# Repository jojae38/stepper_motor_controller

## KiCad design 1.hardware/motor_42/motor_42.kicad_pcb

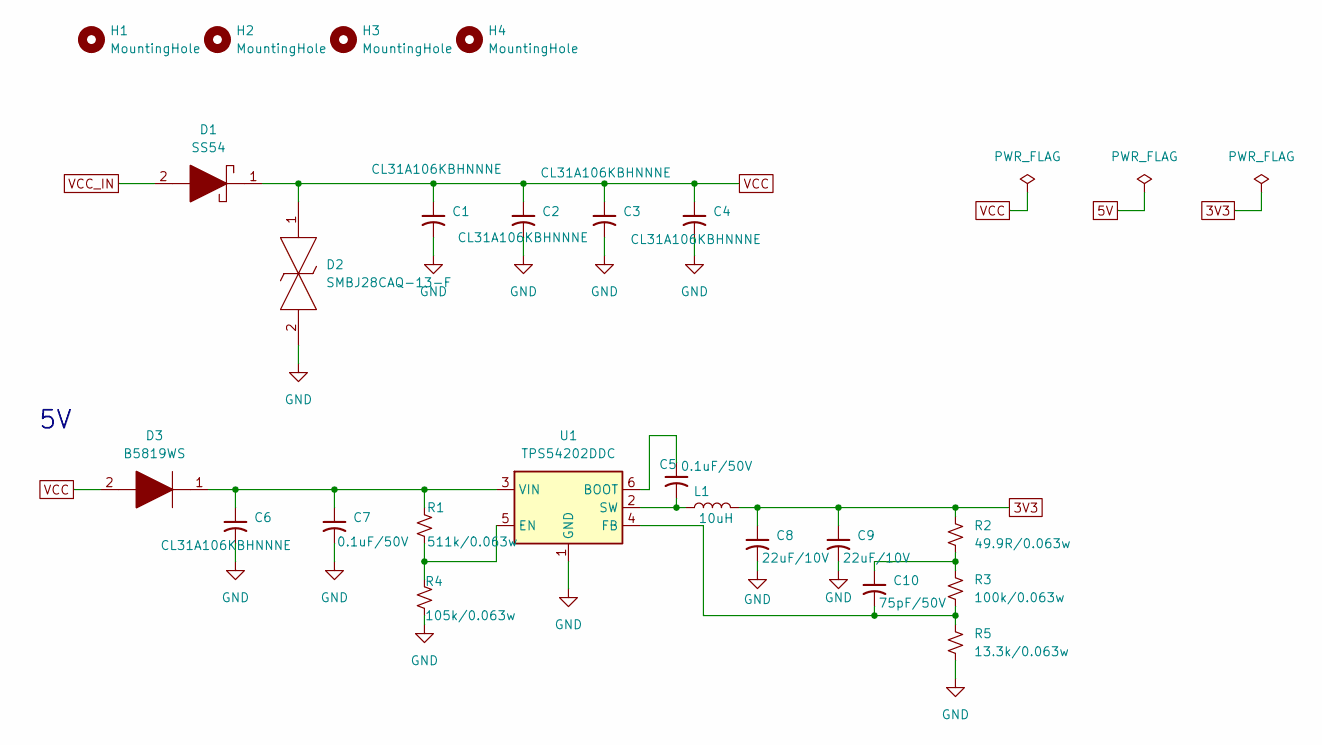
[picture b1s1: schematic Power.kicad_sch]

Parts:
C1, C2, C3, C4, C6: CL31A106KBHNNNE; C_1206_3216Metric
C5, C7: 0.1uF/50V; C_0402_1005Metric
C8, C9: 22uF/10V; C_1206_3216Metric
C10: 75pF/50V; C_0402_1005Metric
D1: SS54; DIOM5126X245N; Manufacturer_Part_Number SS54
D2: SMBJ28CAQ-13-F; DIONM5336X250N; Manufacturer_Part_Number SMBJ28CAQ-13-F; Mouser Part Number 621-SMBJ28CAQ-13-F
D3: B5819WS; D_SOD-323; Manufacturer_Part_Number B5819WS
H1, H2, H3, H4: MountingHole; MountingHole_3.2mm_M3
L1: 10uH; L_Sunlord_SWPA4020S
R1: 511k/0.063w; R_0402_1005Metric
R2: 49.9R/0.063w; R_0402_1005Metric
R3: 100k/0.063w; R_0402_1005Metric
R4: 105k/0.063w; R_0402_1005Metric
R5: 13.3k/0.063w; R_0402_1005Metric
U1: TPS54202DDC; SOT-23-6

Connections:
3V3: C8.1, C9.1, L1.2, R2.1; also elsewhere on the board
GND: C1.2, C2.2, C3.2, C4.2, C6.2, C7.2, C8.2, C9.2, D2.2, R4.2, R5.2, U1.1 (GND); also elsewhere on the board
unnamed: C10.1, R2.2, R3.1
unnamed: C5.1, U1.6 (BOOT)
unnamed: R1.2, R4.1, U1.5 (EN)
unnamed: C10.2, R3.2, R5.1, U1.4 (FB)
unnamed: C5.2, L1.1, U1.2 (SW)
unnamed: C6.1, C7.1, D3.1, R1.1, U1.3 (VIN)
VCC: C1.1, C2.1, C3.1, C4.1, D1.1, D2.1, D3.2; also elsewhere on the board
VCC_IN: D1.2; also elsewhere on the board

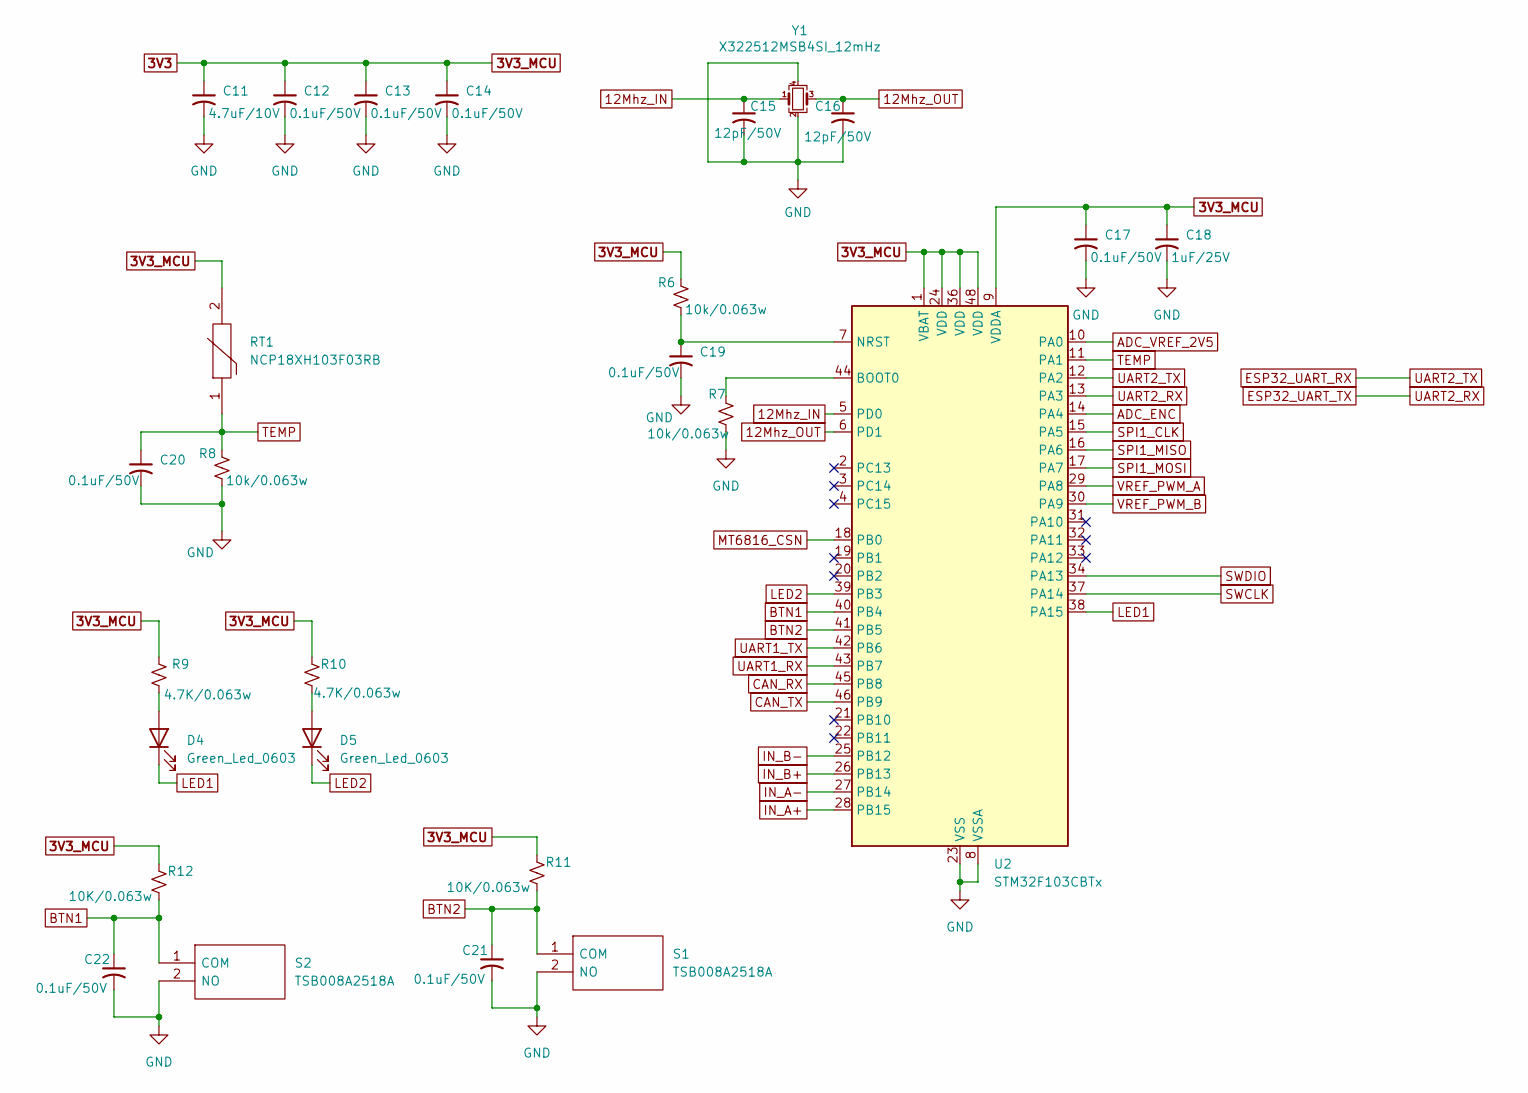
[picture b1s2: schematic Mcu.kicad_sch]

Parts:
C11: 4.7uF/10V; C_0603_1608Metric
C12, C13, C14, C17, C19, C20, C21, C22: 0.1uF/50V; C_0402_1005Metric
C15, C16: 12pF/50V; C_0402_1005Metric
C18: 1uF/25V; C_0402_1005Metric
D4, D5: Green_Led_0603; LED_0603_1608Metric
R6, R7, R8: 10k/0.063w; R_0402_1005Metric
R9, R10: 4.7K/0.063w; R_0402_1005Metric
R11, R12: 10K/0.063w; R_0402_1005Metric
RT1: NCP18XH103F03RB; THRMC1608X95N; Manufacturer_Part_Number NCP18XH103F03RB; Mouser Part Number 81-NCP18XH103F03RB
S1, S2: TSB008A2518A; Manufacturer_Part_Number TSB008A2518A
U2: STM32F103CBTx; LQFP-48_7x7mm_P0.5mm
Y1: X322512MSB4SI_12mHz; Crystal_SMD_3225-4Pin_3.2x2.5mm

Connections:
3V3: C11.1, C12.1, C13.1, C14.1, C17.1, C18.1, R6.2, R9.1, R10.1, R11.1, R12.1, RT1.2, U2.1 (VBAT), U2.9 (VDDA), U2.24 (VDD), U2.36 (VDD), U2.48 (VDD); also elsewhere on the board
12Mhz_IN: C15.1, U2.5 (PD0), Y1.1
12Mhz_OUT: C16.1, U2.6 (PD1), Y1.3
ADC_ENC: U2.14 (PA4); also elsewhere on the board
ADC_VREF_2V5: U2.10 (PA0); also elsewhere on the board
BTN1: C22.1, R12.2, S2.1 (COM), U2.40 (PB4)
BTN2: C21.1, R11.2, S1.1 (COM), U2.41 (PB5)
CAN_RX: U2.45 (PB8); also elsewhere on the board
CAN_TX: U2.46 (PB9); also elsewhere on the board
ESP32_UART_RX: U2.12 (PA2); also elsewhere on the board
ESP32_UART_TX: U2.13 (PA3); also elsewhere on the board
GND: C11.2, C12.2, C13.2, C14.2, C15.2, C16.2, C17.2, C18.2, C19.2, C20.2, C21.2, C22.2, R7.2, R8.1, S1.2 (NO), S2.2 (NO), U2.8 (VSSA), U2.23 (VSS), U2.35 (VSS), U2.47 (VSS), Y1.2, Y1.4; also elsewhere on the board
IN_A+: U2.28 (PB15); also elsewhere on the board
IN_A-: U2.27 (PB14); also elsewhere on the board
IN_B+: U2.26 (PB13); also elsewhere on the board
IN_B-: U2.25 (PB12); also elsewhere on the board
LED1: D4.1 (K), U2.38 (PA15)
LED2: D5.1 (K), U2.39 (PB3)
MT6816_CSN: U2.18 (PB0); also elsewhere on the board
unnamed: D4.2 (A), R9.2
unnamed: D5.2 (A), R10.2
unnamed: R7.1, U2.44 (BOOT0)
unnamed: C19.1, R6.1, U2.7 (NRST)
SPI1_CLK: U2.15 (PA5); also elsewhere on the board
SPI1_MISO: U2.16 (PA6); also elsewhere on the board
SPI1_MOSI: U2.17 (PA7); also elsewhere on the board
SWCLK: U2.37 (PA14); also elsewhere on the board
SWDIO: U2.34 (PA13); also elsewhere on the board
TEMP: C20.1, R8.2, RT1.1, U2.11 (PA1)
UART1_RX: U2.43 (PB7); also elsewhere on the board
UART1_TX: U2.42 (PB6); also elsewhere on the board
VREF_PWM_A: U2.29 (PA8); also elsewhere on the board
VREF_PWM_B: U2.30 (PA9); also elsewhere on the board

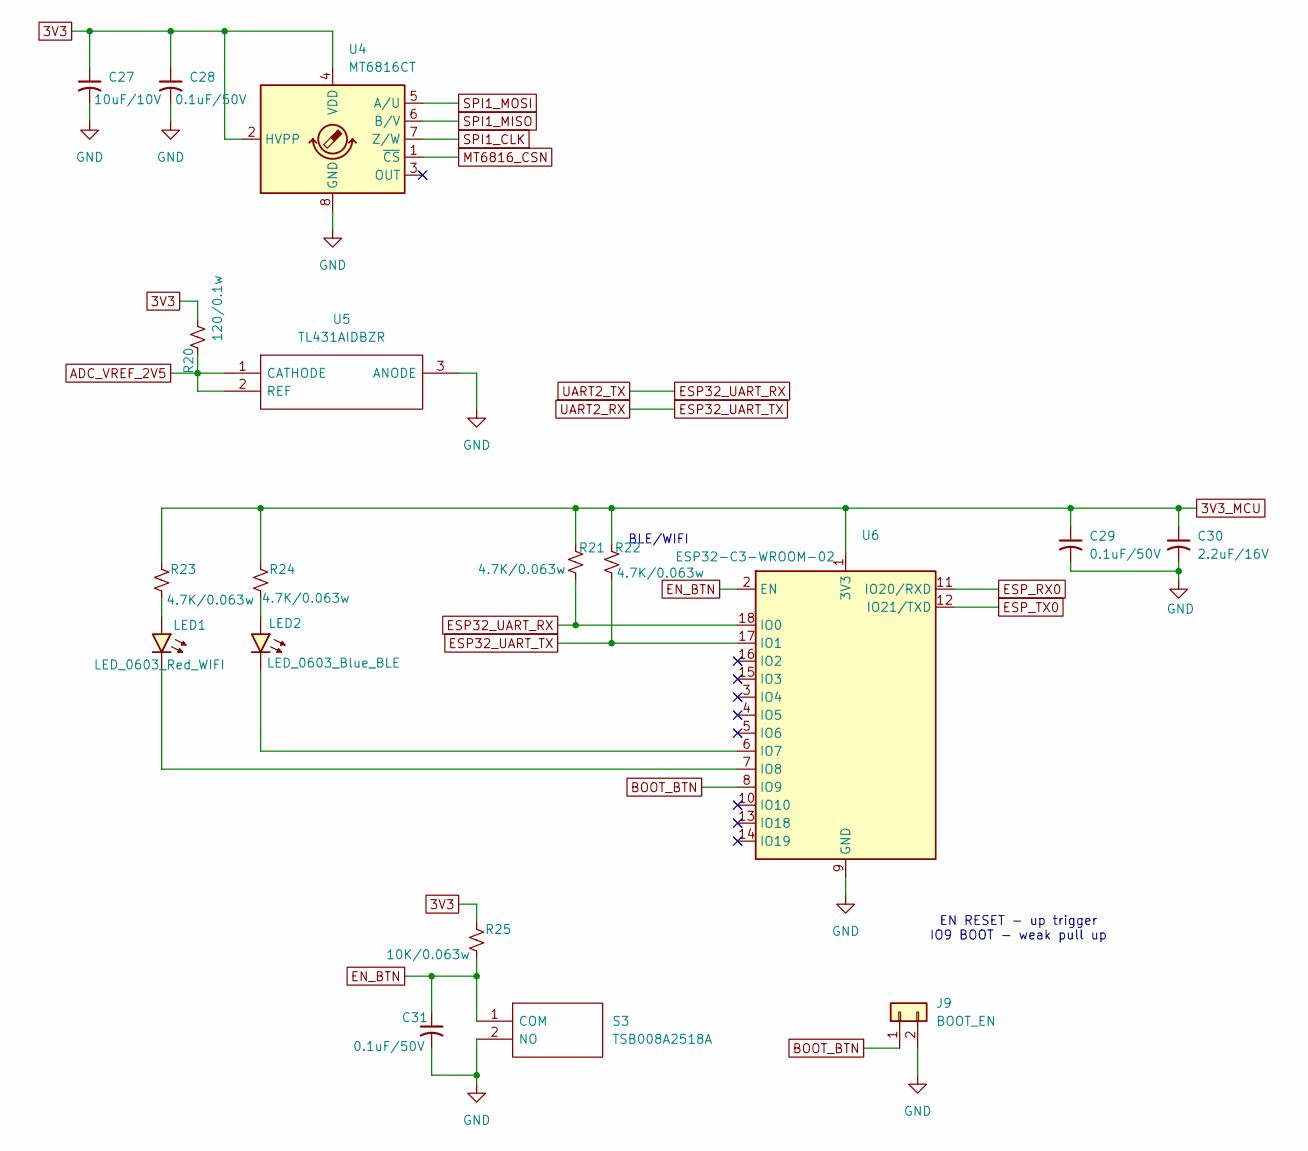
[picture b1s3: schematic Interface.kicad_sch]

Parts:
C27: 10uF/10V; C_0603_1608Metric
C28, C29, C31: 0.1uF/50V; C_0402_1005Metric
C30: 2.2uF/16V; C_0603_1608Metric
J9: BOOT_EN; PinHeader_1x02_P2.54mm_Vertical
LED1: LED_0603_Red_WIFI; LED_0603_1608Metric
LED2: LED_0603_Blue_BLE; LED_0603_1608Metric
R20: 120/0.1w; R_0603_1608Metric
R21, R22, R23, R24: 4.7K/0.063w; R_0402_1005Metric
R25: 10K/0.063w; R_0402_1005Metric
S3: TSB008A2518A; Manufacturer_Part_Number TSB008A2518A
U4: MT6816CT; SO-8_3.9x4.9mm_P1.27mm
U5: TL431AIDBZR; SOT95P237X112-3N; Manufacturer_Part_Number TL431AIDBZR; Mouser Part Number 595-TL431AIDBZR
U6: ESP32-C3-WROOM-02

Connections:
3V3: C27.1, C28.1, C29.1, C30.1, R20.1, R21.1, R22.1, R23.1, R24.1, R25.1, U4.2 (HVPP), U4.4 (VDD), U6.1 (3V3); also elsewhere on the board
ADC_VREF_2V5: R20.2, U5.1 (CATHODE), U5.2 (REF); also elsewhere on the board
BOOT_BTN: J9.1, U6.8 (IO9)
EN_BTN: C31.1, R25.2, S3.1 (COM), U6.2 (EN)
ESP32_UART_RX: R21.2, U6.18 (IO0); also elsewhere on the board
ESP32_UART_TX: R22.2, U6.17 (IO1); also elsewhere on the board
ESP_RX0: U6.11 (IO20/RXD); also elsewhere on the board
ESP_TX0: U6.12 (IO21/TXD); also elsewhere on the board
GND: C27.2, C28.2, C29.2, C30.2, C31.2, J9.2, S3.2 (NO), U4.8 (GND), U5.3 (ANODE), U6.9 (GND), U6.19 (GND); also elsewhere on the board
MT6816_CSN: U4.1 (~CS); also elsewhere on the board
unnamed: LED1.2 (A), R23.2
unnamed: LED1.1 (K), U6.7 (IO8)
unnamed: LED2.2 (A), R24.2
unnamed: LED2.1 (K), U6.6 (IO7)
SPI1_CLK: U4.7 (Z/W); also elsewhere on the board
SPI1_MISO: U4.6 (B/V); also elsewhere on the board
SPI1_MOSI: U4.5 (A/U); also elsewhere on the board

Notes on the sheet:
BLE/WIFI
EN RESET - up trigger IO9 BOOT - weak pull up

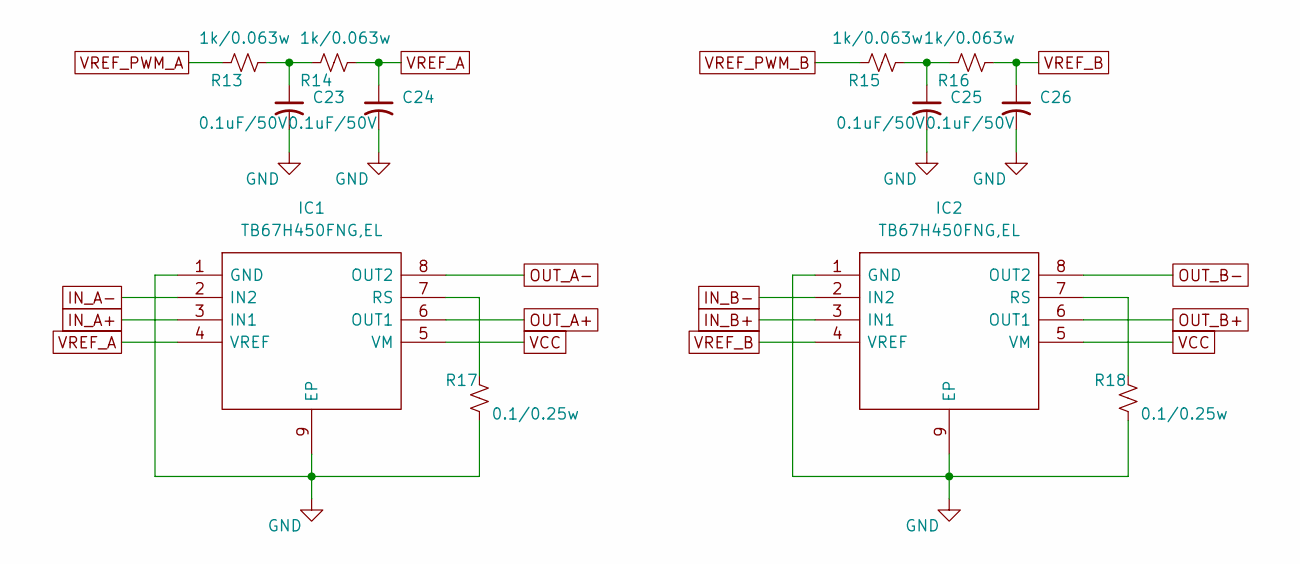
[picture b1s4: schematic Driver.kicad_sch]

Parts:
C23, C24, C25, C26: 0.1uF/50V; C_0402_1005Metric
IC1, IC2: TB67H450FNG,EL; SOIC127P600X175-9N; Manufacturer_Part_Number TB67H450FNG,EL; Mouser Part Number 757-TB67H450FNGEL
R13, R14, R15, R16: 1k/0.063w; R_0402_1005Metric
R17, R18: 0.1/0.25w; R_1206_3216Metric

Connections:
GND: C23.2, C24.2, C25.2, C26.2, IC1.1 (GND), IC1.9 (EP), IC2.1 (GND), IC2.9 (EP), R17.1, R18.1; also elsewhere on the board
IN_A+: IC1.3 (IN1); also elsewhere on the board
IN_A-: IC1.2 (IN2); also elsewhere on the board
IN_B+: IC2.3 (IN1); also elsewhere on the board
IN_B-: IC2.2 (IN2); also elsewhere on the board
unnamed: C23.1, R13.1, R14.2
unnamed: C25.1, R15.1, R16.2
unnamed: IC1.7 (RS), R17.2
unnamed: IC2.7 (RS), R18.2
OUT_A+: IC1.6 (OUT1); also elsewhere on the board
OUT_A-: IC1.8 (OUT2); also elsewhere on the board
OUT_B+: IC2.6 (OUT1); also elsewhere on the board
OUT_B-: IC2.8 (OUT2); also elsewhere on the board
VCC: IC1.5 (VM), IC2.5 (VM); also elsewhere on the board
VREF_A: C24.1, IC1.4 (VREF), R14.1
VREF_B: C26.1, IC2.4 (VREF), R16.1
VREF_PWM_A: R13.2; also elsewhere on the board
VREF_PWM_B: R15.2; also elsewhere on the board

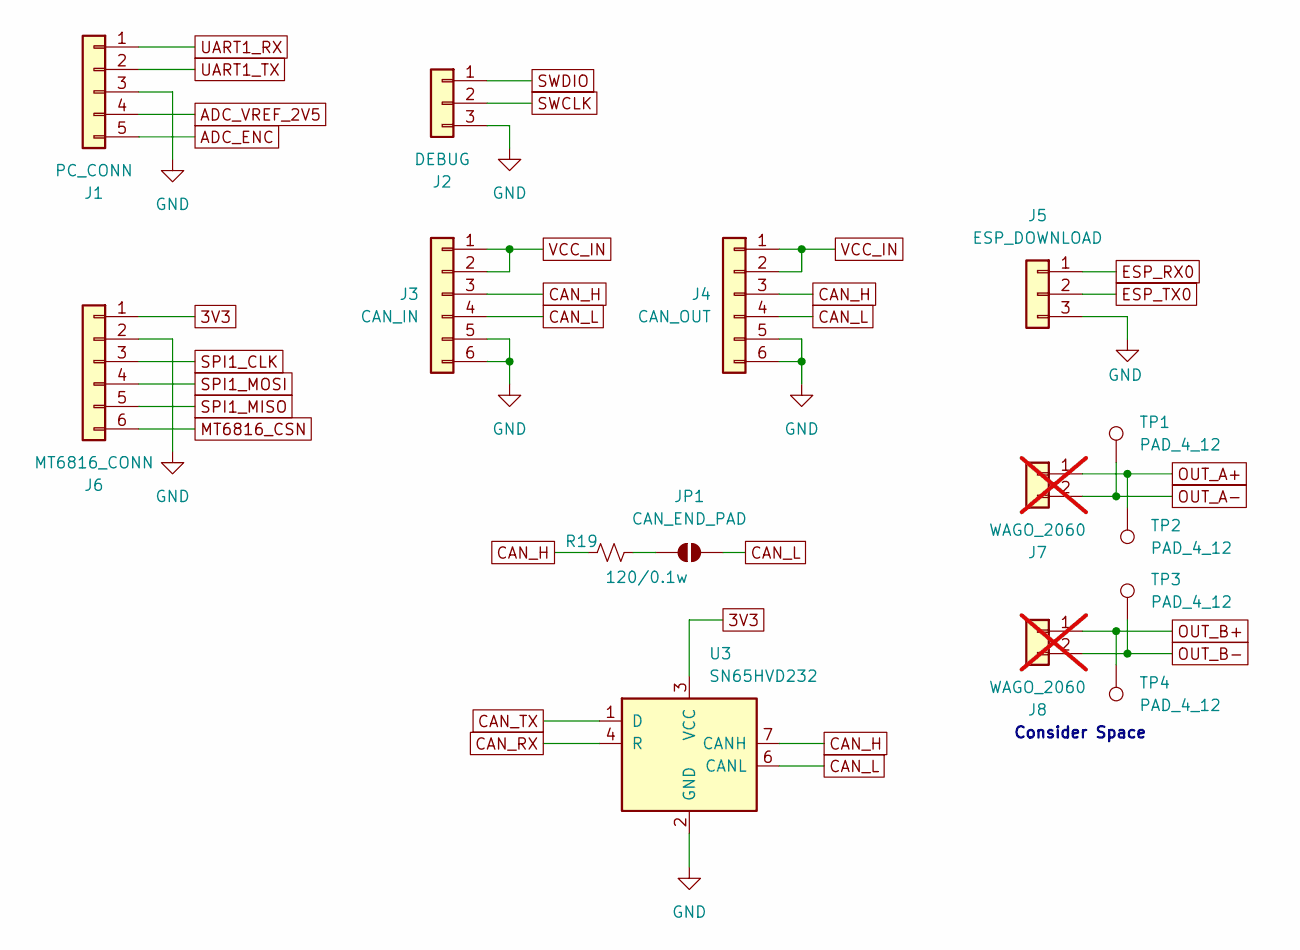
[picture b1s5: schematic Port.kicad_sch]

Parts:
J1: PC_CONN; JST_SH_SM05B-SRSS-TB_1x05-1MP_P1.00mm_Horizontal
J2: DEBUG; JST_SH_SM03B-SRSS-TB_1x03-1MP_P1.00mm_Horizontal
J3: CAN_IN; JST_SH_SM06B-SRSS-TB_1x06-1MP_P1.00mm_Horizontal
J4: CAN_OUT; JST_SH_SM06B-SRSS-TB_1x06-1MP_P1.00mm_Horizontal
J5: ESP_DOWNLOAD; JST_SH_SM03B-SRSS-TB_1x03-1MP_P1.00mm_Horizontal
J6: MT6816_CONN; JST_SH_SM05B-SRSS-TB_1x05-1MP_P1.00mm_Horizontal
J7, J8: WAGO_2060; not fitted
JP1: CAN_END_PAD; SolderJumper-2_P1.3mm_Open_RoundedPad1.0x1.5mm
R19: 120/0.1w; R_0603_1608Metric
TP1, TP2, TP3, TP4: PAD_4_12; custom_pad_2_5
U3: SN65HVD232; SOIC-8_3.9x4.9mm_P1.27mm

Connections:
3V3: J6.1, U3.3 (VCC); also elsewhere on the board
ADC_ENC: J1.5; also elsewhere on the board
ADC_VREF_2V5: J1.4; also elsewhere on the board
CAN_H: J3.3, J4.3, R19.2, U3.7 (CANH)
CAN_L: J3.4, J4.4, JP1.2 (B), U3.6 (CANL)
CAN_RX: U3.4 (R); also elsewhere on the board
CAN_TX: U3.1 (D); also elsewhere on the board
ESP_RX0: J5.1; also elsewhere on the board
ESP_TX0: J5.2; also elsewhere on the board
GND: J1.3, J2.3, J3.5, J3.6, J4.5, J4.6, J5.3, J6.2, U3.2 (GND); also elsewhere on the board
unnamed: JP1.1 (A), R19.1
OUT_A+: J7.1, TP2.1; also elsewhere on the board
OUT_A-: J7.2, TP1.1; also elsewhere on the board
OUT_B+: J8.1, TP4.1; also elsewhere on the board
OUT_B-: J8.2, TP3.1; also elsewhere on the board
SPI1_CLK: J6.3; also elsewhere on the board
SPI1_MISO: J6.5; also elsewhere on the board
SPI1_MOSI: J6.4; also elsewhere on the board
SWCLK: J2.2; also elsewhere on the board
SWDIO: J2.1; also elsewhere on the board
UART1_RX: J1.1; also elsewhere on the board
UART1_TX: J1.2; also elsewhere on the board
VCC_IN: J3.1, J3.2, J4.1, J4.2; also elsewhere on the board

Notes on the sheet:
Consider Space

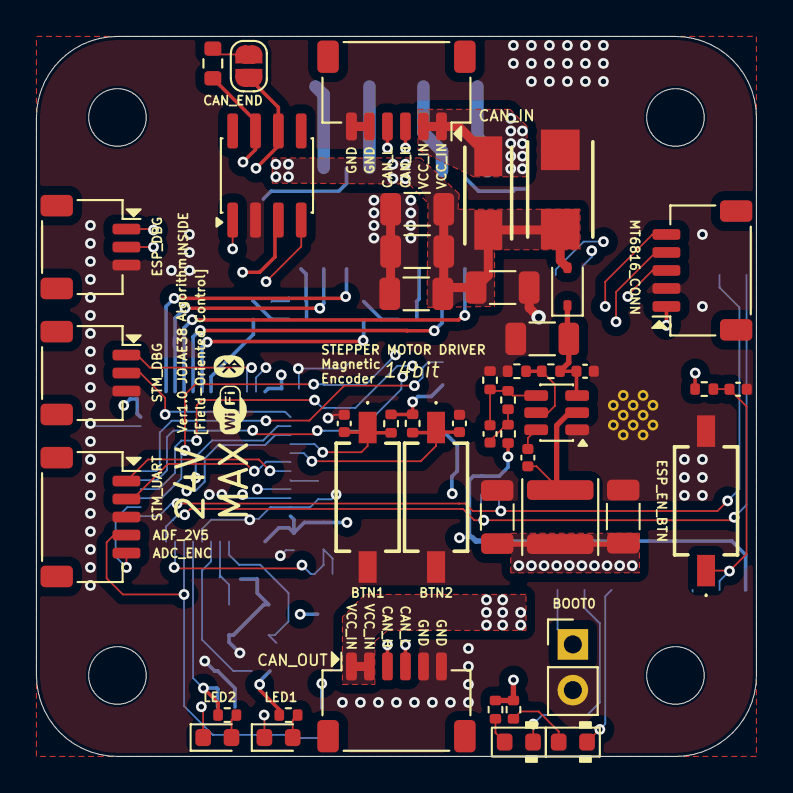
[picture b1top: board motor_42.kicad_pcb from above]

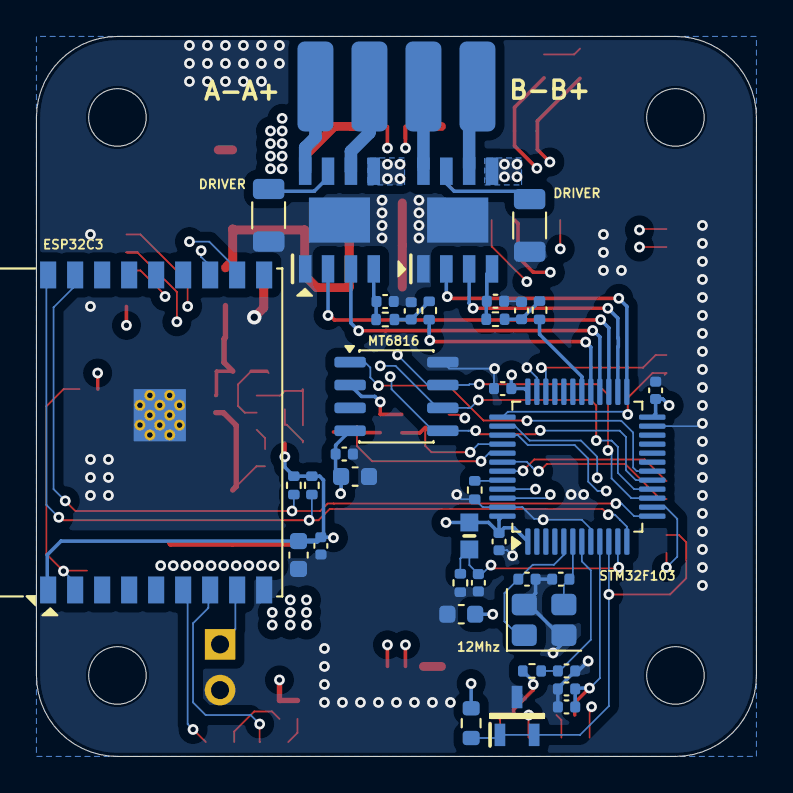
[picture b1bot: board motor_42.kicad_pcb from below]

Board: 4 copper layers, 40.0 x 40.0 mm, 93 parts (42 on the bottom side), 62 nets.

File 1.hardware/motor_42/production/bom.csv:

Designator,Footprint,Quantity,Value,LCSC Part #
"C10, C2, C6, C7, C8",1206,5,CL31A106KBHNNNE,
"C11, C12",1206,2,22uF/10V,
C13,0402,1,75pF/50V,
"C14, C15, C17, C18, C19, C20, C21, C24, C25, C26, C27, C30, C31, C32, C35, C4, C9",0402,17,0.1uF/50V,
C16,0603,1,4.7uF/10V,
"C22, C23",0402,2,12pF/50V,
C28,0603,1,10uF/6.3V,
C33,0603,1,2.2uF/6.3V,
C36,0402,1,1uF/10V,
D2,DIONM5336X250N,1,SMBJ28CAQ-13-F,
D3,D_SOD-323,1,B5819WS,
D4,DIOM5126X245N,1,SS54,
"IC1, IC2",SOIC127P600X175-9N,2,"TB67H450FNG,EL",
J1,JST_SH_SM05B-SRSS-TB_1x05-1MP_P1.00mm_Horizontal,1,PC_CONN,
J2,JST_SH_SM05B-SRSS-TB_1x05-1MP_P1.00mm_Horizontal,1,MT6816_CONN,
J4,JST_SH_SM03B-SRSS-TB_1x03-1MP_P1.00mm_Horizontal,1,DEBUG,
J5,JST_SH_SM06B-SRSS-TB_1x06-1MP_P1.00mm_Horizontal,1,CAN_IN,
J6,JST_SH_SM06B-SRSS-TB_1x06-1MP_P1.00mm_Horizontal,1,CAN_OUT,
J7,JST_SH_SM03B-SRSS-TB_1x03-1MP_P1.00mm_Horizontal,1,ESP_DOWNLOAD,
J8,PinHeader_1x02_P2.54mm_Vertical,1,BOOT_EN,
L2,L_Sunlord_SWPA4020S,1,10uH,
"LED1, LED4",0603,2,LED_0603_Red_WIFI,
"LED2, LED5",0603,2,LED_0603_Blue_BLE,
R1,0402,1,511k/0.063w,
"R10, R11, R13, R14, R15, R32",0402,6,10k/0.063w,
"R12, R28, R31, R33, R34, R9",0402,6,4.7K/0.063w,
"R18, R19, R21, R22",0402,4,1k/0.063w,
R2,0402,1,105k/0.063w,
"R20, R23",1206,2,0.1/0.25w,
"R26, R29",0603,2,120/0.1w,
R6,0402,1,49.9R/0.063w,
R7,0402,1,100k/0.063w,
R8,0402,1,13.3k/0.063w,
RT1,THRMC1608X95N,1,NCP18XH103F03RB,
"S1, S2, S3",TSB008A2518A,3,TSB008A2518A,
"TP1, TP2, TP3, TP4",custom_pad_2_5,4,PAD_4_12,
U1,SOT-23-6,1,TPS54202DDC,
U2,LQFP-48_7x7mm_P0.5mm,1,STM32F103CBTx,
U3,SOIC-8_3.9x4.9mm_P1.27mm,1,SN65HVD232,
U4,SOT95P237X112-3N,1,TL431AIDBZR,
U5,SO-8_3.9x4.9mm_P1.27mm,1,MT6816CT,
U6,ESP32-C3-WROOM-02,1,ESP32-C3-WROOM-02,
Y1,Crystal_SMD_3225-4Pin_3.2x2.5mm,1,YSX321SL_12Mhz,

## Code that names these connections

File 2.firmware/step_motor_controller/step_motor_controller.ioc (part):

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Mcu.Name=STM32F103C(8-B)Tx
Mcu.Package=LQFP48
Mcu.UserName=STM32F103CBTx
PA0-WKUP.GPIOParameters=GPIO_Label
PA0-WKUP.GPIO_Label=ADC1_0_VREF_2V5
PA0-WKUP.Signal=ADCx_IN0
PA1.GPIOParameters=GPIO_Label
PA1.GPIO_Label=ADC1_1_TEMP
PA1.Signal=ADCx_IN1
PA11.GPIOParameters=GPIO_Label
PA11.GPIO_Label=NC_USB_DM
PA11.Mode=Device
PA11.Signal=USB_DM
PA12.GPIOParameters=GPIO_Label
PA12.GPIO_Label=NC_USB_DP
PA12.Mode=Device
PA12.Signal=USB_DP
PA13.Mode=Serial_Wire
PA13.Signal=SYS_JTMS-SWDIO
PA14.Mode=Serial_Wire
PA14.Signal=SYS_JTCK-SWCLK
PA15.GPIOParameters=PinState,GPIO_Label
PA15.GPIO_Label=LED1
PA15.PinState=GPIO_PIN_SET
PA15.Signal=GPIO_Output
PA2.GPIOParameters=GPIO_Label
PA2.GPIO_Label=UART2_TX_ESP32
PA2.Mode=Asynchronous
PA2.Signal=USART2_TX
PA3.GPIOParameters=GPIO_Label
PA3.GPIO_Label=UART2_RX_ESP32
PA3.Mode=Asynchronous
PA3.Signal=USART2_RX
PA4.GPIOParameters=GPIO_Label
PA4.GPIO_Label=ADC_ENC
PA4.Signal=GPIO_Output
PA5.Mode=Full_Duplex_Slave
PA5.Signal=SPI1_SCK
PA6.Mode=Full_Duplex_Slave
PA6.Signal=SPI1_MISO
PA7.Mode=Full_Duplex_Slave
PA7.Signal=SPI1_MOSI
PA8.GPIOParameters=GPIO_Label
PA8.GPIO_Label=VREF_PWM_A
PA8.Signal=S_TIM1_CH1
PA9.GPIOParameters=GPIO_Label
PA9.GPIO_Label=VREF_PWM_B
PA9.Signal=S_TIM1_CH2
PB0.GPIOParameters=GPIO_Label
PB0.GPIO_Label=MT6816_CSN
PB0.Signal=GPIO_Output
PB12.GPIOParameters=GPIO_Label
PB12.GPIO_Label=IN_B_M
PB12.Signal=GPIO_Output
PB13.GPIOParameters=GPIO_Label
PB13.GPIO_Label=IN_B_P
PB13.Signal=GPIO_Output
PB14.GPIOParameters=GPIO_Label
PB14.GPIO_Label=IN_A_M
PB14.Signal=GPIO_Output
PB15.GPIOParameters=GPIO_Label
PB15.GPIO_Label=IN_A_P
PB15.Signal=GPIO_Output
PB3.GPIOParameters=PinState,GPIO_Label
PB3.GPIO_Label=LED2
PB3.PinState=GPIO_PIN_SET
PB3.Signal=GPIO_Output
PB4.GPIOParameters=GPIO_Label
PB4.GPIO_Label=BTN1
PB4.Signal=GPIO_Input
PB5.GPIOParameters=GPIO_Label
PB5.GPIO_Label=BTN2
PB5.Signal=GPIO_Input
PB6.Mode=Asynchronous
PB6.Signal=USART1_TX
PB7.Mode=Asynchronous
PB7.Signal=USART1_RX
PB8.Mode=CAN_Activate
PB8.Signal=CAN_RX
PB9.Mode=CAN_Activate
PB9.Signal=CAN_TX
PD0-OSC_IN.Mode=HSE-External-Oscillator
PD0-OSC_IN.Signal=RCC_OSC_IN
PD1-OSC_OUT.Mode=HSE-External-Oscillator
PD1-OSC_OUT.Signal=RCC_OSC_OUT
RCC.HSE_VALUE=12000000
RCC.SYSCLKFreq_VALUE=72000000
RCC.SYSCLKSource=RCC_SYSCLKSOURCE_PLLCLK
board=custom

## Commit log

2025-11-09 first_commit
2025-11-18 중간 저장
2025-11-26 살짝 변경
2025-11-27 작은 변경
2025-11-29 회로도 대충 완성
2025-11-30 3V3 LDO변경 및 대략적 위치 세팅
2025-12-01 얼추 다 그림
2025-12-01 실크 업데이트
2025-12-01 비아 변경 필요
2025-12-02 via 홀 0.3 직경 0.6(1.5의 폭 을 가진다) 수정 및 라우팅 개선
2025-12-02 wifi ble 문양 추가
2025-12-02 번호 초기화 및 led 변경
2025-12-04 생산파일
2026-01-06 코드 추가
2026-01-08 기본 코드 구조 생성
2026-01-08 중간 수정
2026-01-13 cli 기능 추가
2026-01-18 검증 및 수정
2026-01-19 CLI 항목 추가
